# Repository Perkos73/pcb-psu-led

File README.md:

# PCB PSU LED

Moduł zasilania i sterowania diody LED dla customowego zasilacza step-down 230 V → 100 V.

## Status projektu

- Aktualna rewizja elektryczna: **ECAD-19**
- Ostatnia rewizja dokumentacji: **DOC-07**
- Schemat: **KOMPLETNY — 12 z 12 pozycji**
- Footprinty: **KOMPLETNE — 12 z 12 przypisanych, 10 plików w `PSU_LED.pretty/`**
- Etap 1 (schemat) — **zamknięty**
- Etap 2 (footprinty) — **zamknięty**
- Etap 3 (PCB) — **w toku**: netclasy i reguły DRC gotowe, layout czeka
- ERC bramkujący: **0 errors / 0 warnings**
- Pełny ERC: **0 errors / 0 warnings**
- Walidacja: wyłącznie przez **GitHub Actions**
- Wersja KiCad w CI: **10.0.4** (obraz `ghcr.io/kicad/kicad:10.0-full`, wersja raportowana w runtime)
- Gałąź robocza: `main`
- Gałąź `pcb2`: równoległy projekt drugiego zespołu, wspólny przodek ECAD-11 — **nie mergować**

Obsada: `J1`, `F1`, `T1`, `D1`, `D2`, `C1`, `C2`, `U1`, `C3`, `R1`, `RV1`, `J2`.
Dioda `Kingbright L-7104EC` znajduje się na panelu przednim, poza płytką — wychodzi przez `J2`.

## Zatwierdzona topologia

### Wejście sieciowe

Lokalny symbol:

- `J1`
- `J1.1 = L_SW`
- `J1.2 = N_SW`

Aktualne połączenia:

- `J1.1 → L_SW → F1.1`
- `F1.2 → L_FUSED → T1.6`
- `J1.2 → N_SW → T1.3`
- `T1.5 ↔ T1.4 = PRI_LINK_5_4`

Bezpiecznik `F1` wyłącznie w przewodzie fazowym. Neutralny bez zabezpieczenia —
rozłączanie obu przewodów realizuje wyłącznik NKK M2022SS4W01 (DPDT).

### Transformator

- `T1 = Talema 70000K`
- moc znamionowa: `1.6 VA`
- dwa uzwojenia pierwotne `115 V`
- dwa uzwojenia wtórne `7 V`
- lokalny symbol i footprint przechodzą walidację CI

### Uzwojenie wtórne i prostownik

- `T1.12 ↔ T1.13 = CT_RAW`
- `T1.11 → SEC_A → anoda D2`
- `T1.14 → SEC_B → anoda D1`
- katody `D1` i `D2 → VRAW_PLUS`
- `D1`, `D2 = BYV26C`

### Kondensator zbiorczy

- `C1 = 47 µF / 25 V Panasonic FR`
- `C1 (+) → VRAW_PLUS`
- `C1 (−) → CT_RAW`

### Stabilizator

- `U1 = LM78L05ACZ`
- `U1.3 VIN → VRAW_PLUS`
- `U1.2 GND → CT_RAW`
- `U1.1 VOUT → PLUS_5V_LED`

Pinout projektu:

```text
1 = VOUT
2 = GND
3 = VIN
```

## Pliki projektu

- `pcb-psu-led.kicad_pro` — plik projektu KiCad
- `pcb-psu-led.kicad_sch` — schemat
- `pcb-psu-led.kicad_sym` — lokalna biblioteka symboli
- `PSU_LED.pretty/Talema_70000K.kicad_mod` — lokalny footprint transformatora
- `sym-lib-table` — mapowanie lokalnej biblioteki symboli
- `fp-lib-table` — mapowanie lokalnej biblioteki footprintów
- `.github/workflows/kicad-validate.yml` — workflow walidacyjny
- `README.md` — dokumentacja zatwierdzonego stanu projektu
- `docs/platform.md` — fakty źródłowe: karta 700xxK, ograniczenia `Rev. 6.4.1`,
  macierz wariantów, reguły platformowe

## Walidacja CI

Workflow korzysta z:

- `ghcr.io/kicad/kicad:10.0-full`
- `actions/checkout@v6`
- `actions/upload-artifact@v7`
- zapisywalnej kopii projektu w `RUNNER_TEMP`

Walidowane są:

1. obecność wymaganych plików,
2. wersja KiCad,
3. parsowanie i eksport lokalnego symbolu,
4. parsowanie i eksport footprintu,
5. eksport netlisty,
6. pełny ERC,
7. bramkujący ERC dla błędów.

Raport bramkujący oraz pełny raport ERC są publikowane bezpośrednio w **GitHub Step Summary**.

Aktualny wynik:

```text
Validation exit code: 0
ERC gating report:    0 errors / 0 warnings
Full ERC report:      0 errors / 1 warning
Warning:              PLUS_5V_LED connected to only one pin
```

## Zasady pracy

- jedna logiczna zmiana na commit,
- bez lokalnej walidacji,
- walidacja wyłącznie przez GitHub Actions,
- bez ZIP-ów,
- pliki przekazywane pojedynczo z kanonicznymi nazwami,
- bez dużych generatorów i masowego nadpisywania plików,
- zmiany w kilku plikach należące do jednego ECO muszą trafić do jednego commitu,
- przed kolejnym etapem należy sprawdzić pełny raport ERC w Step Summary.

## Historia rewizji

### ECAD-08

- zapis `pin_names` J1 znormalizowany do formy `(hide yes)`
- zmiana nie usunęła ostrzeżenia `lib_symbol_mismatch`

### ECAD-09

- pole `Datasheet` symbolu `Conn_01x02` ujednolicone do pustego ciągu `""`
- usunięto `lib_symbol_mismatch`
- ERC osiągnął `0 errors / 0 warnings`

### ECAD-10

- dodano kondensator zbiorczy `C1`
- `C1 = 47 µF / 25 V Panasonic FR`
- połączenie między `VRAW_PLUS` i `CT_RAW`
- ERC: `0 errors / 0 warnings`

### ECAD-11

- dodano stabilizator `U1 = LM78L05ACZ`
- `VIN → VRAW_PLUS`
- `GND → CT_RAW`
- `VOUT → PLUS_5V_LED`
- ERC bramkujący: `0 errors`
- pełny ERC: jedno oczekiwane ostrzeżenie dla tymczasowo jednoelementowej sieci `PLUS_5V_LED`

### CI-04

- rozszerzono `kicad-validate.yml` o dwie bramki, bez zmiany istniejacej logiki ERC:
  - **kontrola BOM**: `kicad-cli sch export bom` + wykrycie pustego pola `Footprint`
    → nowy kod wyjscia `70`. To jest bramka, ktora zlapalaby ECAD-19 (commit
    "assign footprints" przeszedl wtedy na zielono, nie przypisawszy niczego,
    bo ERC nie widzi footprintow)
  - **DRC warunkowy**: jesli `pcb-psu-led.kicad_pcb` istnieje →
    `kicad-cli pcb drc --severity-error` z regulami z `mains.kicad_dru`
    → kody `71` (naruszenia) / `72` (brak raportu). Dopoki plytki nie ma,
    krok grzecznie sie pomija
- bariera 6 mm z ECAD-20 staje sie egzekwowalna automatycznie w momencie,
  gdy powstanie layout

### ECAD-20

- zdefiniowano klasy sieci w `pcb-psu-led.kicad_pro`:
  - **MAINS** (`L_SW`, `N_SW`, `L_FUSED`, `PRI_LINK_5_4`): ścieżka min. 1 mm,
    clearance 0.5 mm, kolor czerwony
  - **SELV** (`SEC_A`, `SEC_B`, `CT_RAW`, `VRAW_PLUS`, `LED_R`, `LED_A`,
    `PLUS_5V_LED`): ścieżka 0.5 mm, kolor zielony
- dodano `mains.kicad_dru` — reguły bezpieczeństwa sieciowego jako maszynowa bramka:
  - `mains_to_selv_reinforced`: bariera **MAINS ↔ SELV ≥ 6 mm** (IEC 62368-1,
    izolacja wzmocniona)
  - `mains_internal_clearance`: L ↔ N ≥ 2.5 mm
  - `mains_min_track`: ścieżki MAINS ≥ 1 mm, zero neck-down
  - `mains_to_edge`: miedź MAINS ≥ 2 mm od krawędzi
  - `mains_to_hole`: miedź MAINS ≥ 3 mm od otworów
- 6 mm przestaje być zapisem w dokumencie — staje się regułą, przez którą
  płytka nie przejdzie DRC

### ECAD-19

- przypisano footprinty do wszystkich 12 pozycji schematu
- przypisanie **wyłącznie na instancjach** — symbole `R`, `C`, `Fuse`, `Conn_01x02`
  i pozostałe generyczne zostają bez footprintu, żeby biblioteka nadawała się
  do kolejnych projektów; `lib_symbols` nietknięte → zero ryzyka `lib_symbol_mismatch`
- kontrola: każdy przypisany footprint istnieje w `PSU_LED.pretty/`; żaden plik
  biblioteki nie jest nieużywany
- kontrola pin↔pad: `F1` 1/2 (dwa pady „2" równolegle + NPTH oprawki),
  `U1` 1/2/3, `RV1` 1/2/3, reszta 1/2 — wszystkie zgodne z symbolami

### ECAD-18

- `TerminalBlock_Phoenix_MKDS-1,5-2-5.08_1x02_P5.08mm_Horizontal` dla `J1`
- dwubiegunowy bloczek śrubowy, raster 5.08 mm, przewód do 1.5 mm², pad Ø2.6, wiertło Ø1.3
- Phoenix COMBICON PC 6 (raster 10.16) **nie istnieje** w bibliotece stockowej —
  wspólność z `J_IN`/`J_OUT` z ANEKS 8.1 P2-R4.1 niemożliwa

### ECAD-17

- import 8 footprintów ze stockowych bibliotek zamrożonego obrazu `10.0.4`
- pliki kopiowane bez zmian, weryfikacja bajt w bajt; repo pozostaje samowystarczalne
- `U1` → `TO-92_Wide`: rozgięcie nóżek do 2.54 daje 1.04 mm przerwy między padami
  zamiast 0.17 mm; pad 1 prostokątny = pin 1, sito = płaska ścianka (kontrola lustra OK)
- `F1` → oprawka Schurter FUP **zamknięta** („Shock-Safe"): wymiana bezpiecznika
  bez dostępu do metalu pod napięciem; koszt — ~45 mm długości sektora sieciowego

### ECAD-16

- dodano gałąź diody LED: `R1`, `RV1`, `J2` — **schemat kompletny**
- nowe lokalne symbole `R` i `R_Potentiometer` w `pcb-psu-led.kicad_sym`
  i w `lib_symbols` schematu
- `J2` wykorzystuje istniejący symbol `Conn_01x02` z nadpisaniem `Value` na poziomie
  instancji — bez tworzenia zbędnego symbolu
- tor: `PLUS_5V_LED → R1 → LED_R → RV1.1`; `RV1.2 ↔ RV1.3 → LED_A → J2.1`; `J2.2 → CT_RAW`
- suwak `RV1.2` zwarty z końcem `RV1.3` — reostat z zabezpieczeniem przed utratą
  styku suwaka (rozwarcie suwaka nie gasi diody, tylko ustawia maksymalną rezystancję)
- `R1 = 680 Ω / 0.6 W` — **FROZEN** wg `Rev. 6.4.1` poz. `E-09`, zakaz 560 Ω
- prąd: `(5 − 1.9) / 680 ≈ 4.6 mA` maks., z `RV1` w szeregu do `~0.3 mA`
  → wymóg `I_f < 1 mA` osiągalny pokrętłem
- podstawa: `Rev. 6.4.1` §3.4 oraz poz. `E-04`, `E-09`, `E-10`

### ECAD-15

- dodano kondensatory odsprzęgające stabilizatora: `C2`, `C3 = 100 nF X7R`
- nowy lokalny symbol `C` (niespolaryzowany) w `pcb-psu-led.kicad_sym`
  i w `lib_symbols` schematu
- `C2`: `VRAW_PLUS ↔ CT_RAW`, wejście `U1.3`
- `C3`: `PLUS_5V_LED ↔ CT_RAW`, wyjście `U1.1`
- podstawa: `Rev. 6.4.1` poz. `E-08` (2 szt. 100 nF X7R)
- `C3` domknął sieć `PLUS_5V_LED` drugim pinem → ostrzeżenie `isolated_pin_label` znika
- schemat: 9 z 11 pozycji

### ECAD-14

- dodano bezpiecznik pierwotny `F1 = T32 mA / 250 V` zwłoczny
- nowy lokalny symbol `Fuse` w `pcb-psu-led.kicad_sym` i w `lib_symbols` schematu
- tor fazowy rozdzielony na dwie sieci: `L_SW` (J1.1 → F1.1) i `L_FUSED` (F1.2 → T1.6)
- podstawa: karta 700xxK, `230V Fuse mA (Max.)` = `32 mA` dla rodziny `1.6 VA`
- zamrożony `T500 mA` w module SCI PC-5 jest `15.6×` powyżej maksimum producenta
  i nie zareaguje na awarię tego transformatora
- `J1`, `T1`, przewód neutralny, mostek `T1.5 ↔ T1.4` i strona wtórna — bez zmian
- obudowa (`5×20` vs `TR5`) rozstrzygana na etapie placementu; symbol wspólny

### ECAD-13

- `pcb-psu-led.kicad_sch:890` — instancja `J1`, pole `Datasheet` `"~"` → `""`
- usunięto ostatni legacy placeholder w projekcie
- ERC bez zmian: `0 errors / 1 warning`

### ECAD-12

- footprint `Talema_70000K`: wiertło padów sygnalowych `Ø1.3` → `Ø1.5`
- podstawa: karta 700xxK — pin `1.0 x 0.5 mm` prostokątny, przekątna `1.118 mm`
- `Ø1.3` dawało `0.09 mm` luzu promieniowego (minimum bezwzględne IPC); `Ø1.5` daje `0.19 mm`
- pierścień przy padzie `Ø3.0` pozostaje `0.75 mm`
- współrzędne padów, maska, NPTH i strefy — bez zmian
- `descr` uzupełniony o dane z karty i regułę placementu (`rot=180`)
- zmiana wpływa na fabrykację, nie na ERC

## Następny etap

**Etapy 1 i 2 zamknięte.** Schemat kompletny, footprinty przypisane, ERC `0/0`.

**Etap 3 — PCB**

```text
netclasy MAINS / SELV
mains.kicad_dru — bariera MAINS <-> SELV >= 6 mm (IEC 62368-1, izolacja wzmocniona)
obrys i mocowanie
placement: 230 V z lewej -> 5 V z prawej -> LED; T1 w osi X = 162.50 (Rev. 6.4.1 §2.2)
routing
DRC w CI jako bramka
```

## Walidacja lokalna

Repozytorium jest otwierane w GitHub Codespaces. Obraz KiCada jest dostępny przez
Dockera, więc ERC można uruchomić **przed** commitem:

```bash
./check.sh
```

Skrypt używa dokładnie tego samego obrazu i tej samej komendy co CI.
CI pozostaje bramką — `check.sh` służy do złapania błędu, zanim trafi do historii.

## Dokumenty źródłowe

- `docs/platform.md` — fakty z karty 700xxK, ograniczenia `Rev. 6.4.1`,
  macierz wariantów, reguły platformowe, pozycje otwarte.
  **Czytać przed każdą zmianą projektową.**

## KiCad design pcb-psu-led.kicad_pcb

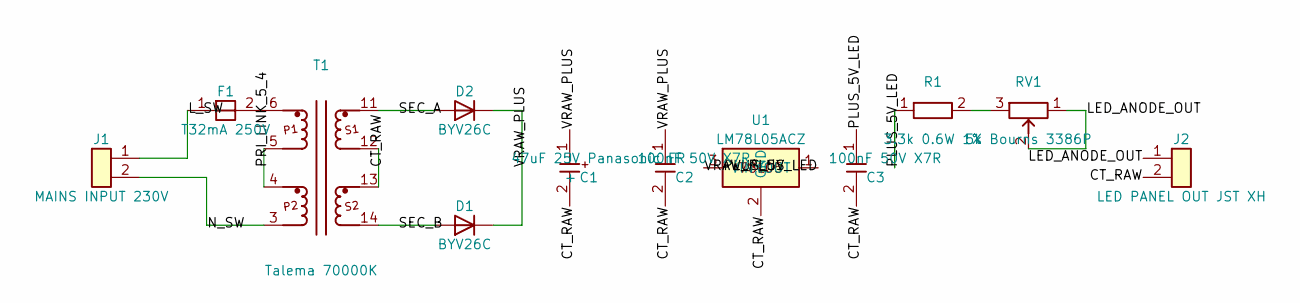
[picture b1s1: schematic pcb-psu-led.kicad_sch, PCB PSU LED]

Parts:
C1: 47uF 25V Panasonic FR; CP_Radial_D5.0mm_P2.00mm; MPN EEUFR1E470
C2, C3: 100nF 50V X7R; C_Disc_D5.0mm_W2.5mm_P2.50mm; MPN C315C104K5R5TA
D1, D2: BYV26C; D_DO-15_P10.16mm_Horizontal; MPN BYV26C
F1: T32mA 250V; Fuseholder_Cylinder-5x20mm_Schurter_0031_8201_Horizontal_Op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; MPN 0031.8201
J1: MAINS INPUT 230V; TerminalBlock_Phoenix_MKDS-1,5-2-5.08_1x02_P5.08mm_Horizont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; MPN 1715721
J2: LED PANEL OUT JST XH; JST_XH_B2B-XH-A_1x02_P2.50mm_Vertical; MPN B2B-XH-A(LF)(SN)
R1: 3.3k 0.6W 1%; R_Axial_DIN0207_L6.3mm_D2.5mm_P10.16mm_Horizontal; MPN MRS25000C3301FCT00
RV1: 5k Bourns 3386P; Potentiometer_Bourns_3386P_Vertical; MPN 3386P-1-502LF
T1: Talema 70000K; Talema_70000K; MPN 70000K
U1: LM78L05ACZ; TO-92_Inline; MPN LM78L05ACZ/NOPB

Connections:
/CT_RAW: C1.2 (-), C2.2, C3.2, J2.2 (CATHODE), T1.12 (S1_END), T1.13 (S2_START), U1.2 (GND)
/LED_ANODE_OUT: J2.1 (ANODE), RV1.1 (CCW), RV1.2 (WIPER)
/L_SW: F1.1, J1.1
/N_SW: J1.2, T1.3 (P2_END)
/PLUS_5V_LED: C3.1, R1.1, U1.1 (VOUT)
/PRI_LINK_5_4: T1.4 (P2_START), T1.5 (P1_END)
/SEC_A: D2.2 (A), T1.11 (S1_START)
/SEC_B: D1.2 (A), T1.14 (S2_END)
/VRAW_PLUS: C1.1 (+), C2.1, D1.1 (K), D2.1 (K), U1.3 (VIN)
unnamed: R1.2, RV1.3 (CW)
unnamed: F1.2, T1.6 (P1_START)

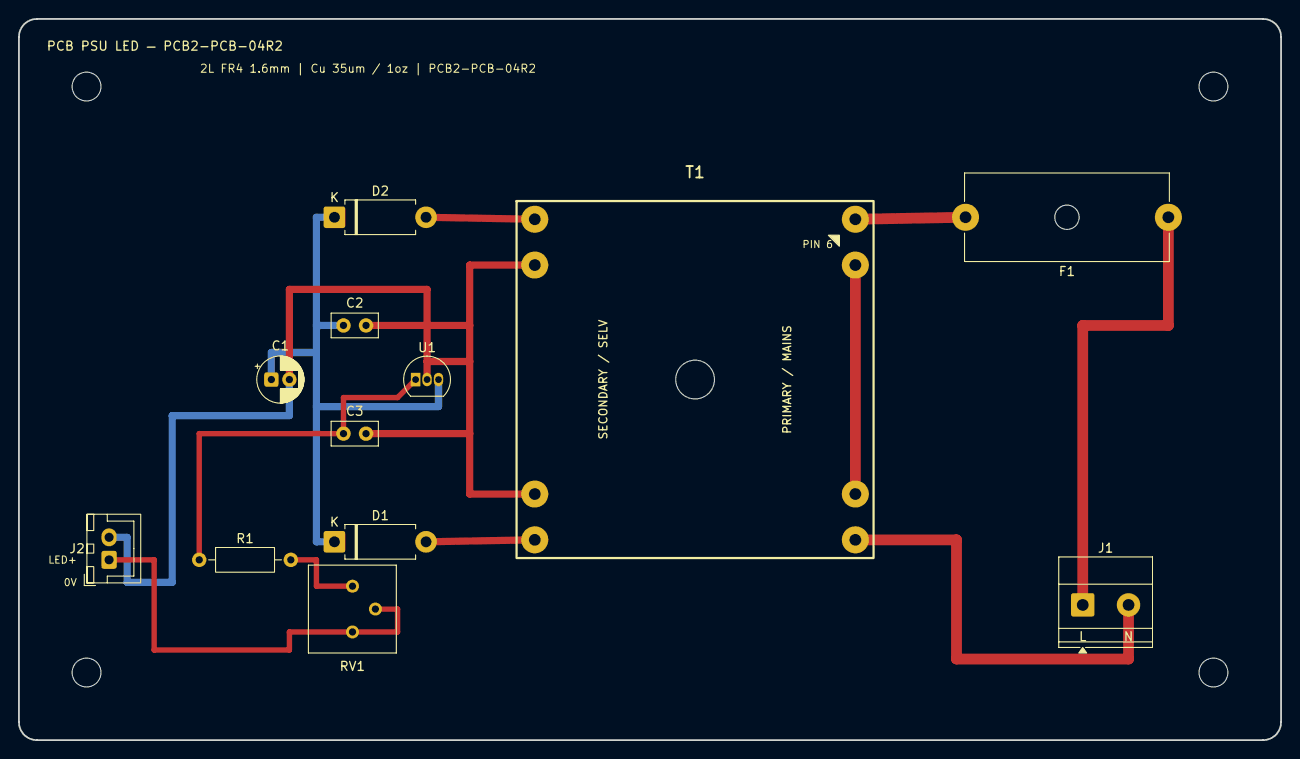
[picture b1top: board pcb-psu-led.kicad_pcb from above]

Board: 2 copper layers, 140.0 x 80.0 mm, 16 parts (0 on the bottom side), 11 nets.

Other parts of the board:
H1, H2, H3, H4: MountingHole_3.2mm_M3
